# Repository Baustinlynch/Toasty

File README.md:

# Toasty Pad

## Features

- 3×3 grid
- 9 keys
- Minimalist design
- Keys can be programmed with macros using QMK

## PCB

I made my PCB using KiCad.

/\ PCB uses a ground plane so it looks like the gnd pins are not connected but they are :)

> This probably breaks many schematic/layout rules, but it looks like it will work.

## CAD

Printed in two pieces; looks pretty good. Made in Onshape.

## Firmware

This project uses QMK firmware included in this repository.

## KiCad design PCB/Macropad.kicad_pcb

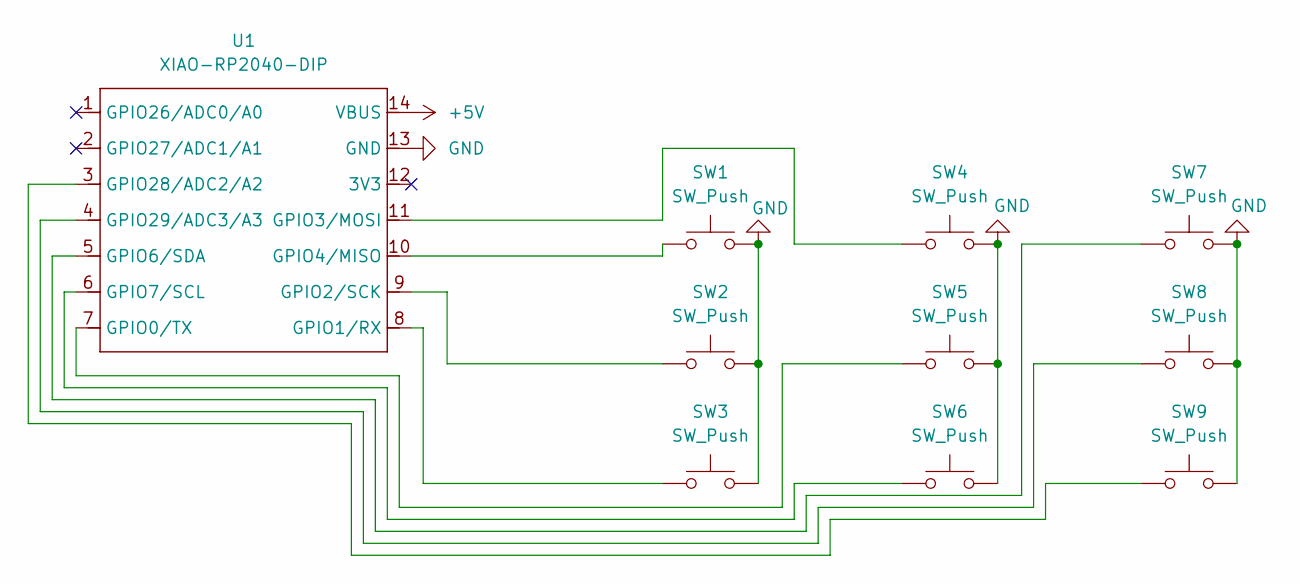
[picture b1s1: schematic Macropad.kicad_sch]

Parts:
SW1, SW2, SW3, SW4, SW5, SW6, SW7, SW8, SW9: SW_Push; SW_Cherry_MX_1.00u_PCB
U1: XIAO-RP2040-DIP

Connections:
+5V: U1.14 (VBUS)
GND: SW1.2, SW2.2, SW3.2, SW4.2, SW5.2, SW6.2, SW7.2, SW8.2, SW9.2, U1.13 (GND)
unnamed: SW5.1, U1.7 (GPIO0/TX)
unnamed: SW3.1, U1.8 (GPIO1/RX)
unnamed: SW2.1, U1.9 (GPIO2/SCK)
unnamed: SW4.1, U1.11 (GPIO3/MOSI)
unnamed: SW1.1, U1.10 (GPIO4/MISO)
unnamed: SW7.1, U1.5 (GPIO6/SDA)
unnamed: SW6.1, U1.6 (GPIO7/SCL)
unnamed: SW9.1, U1.3 (GPIO28/ADC2/A2)
unnamed: SW8.1, U1.4 (GPIO29/ADC3/A3)

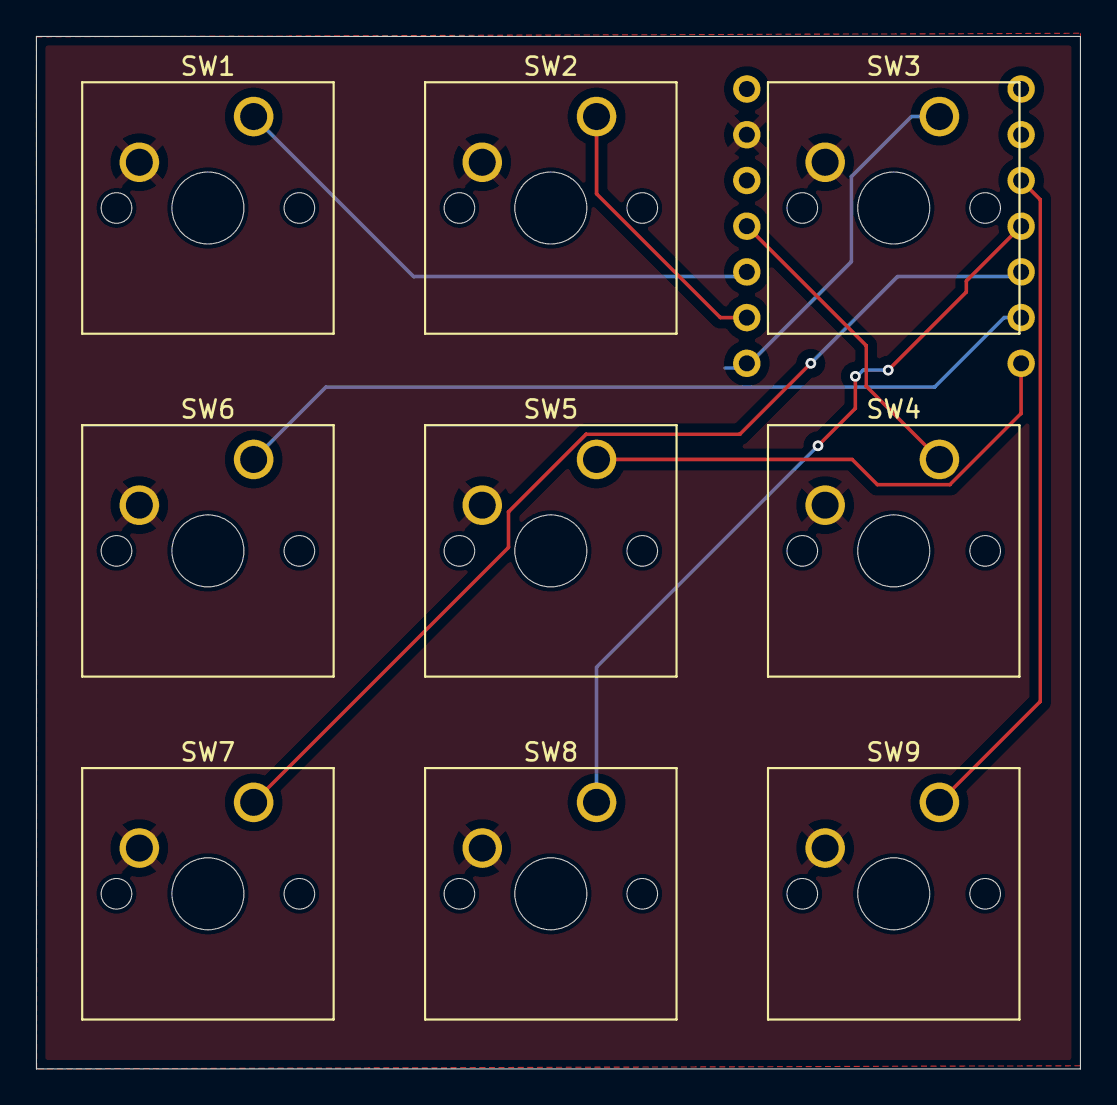
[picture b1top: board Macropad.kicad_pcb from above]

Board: 2 copper layers, 58.0 x 57.4 mm, 10 parts (1 on the bottom side), 10 nets.

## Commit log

2025-12-06 Create cad
2025-12-06 uploaded assembled
2025-12-06 Create pcb
2025-12-06 Create firm
2025-12-11 changed readme
2025-12-11 changes readme
2025-12-11 updated read me and added exploded assembly image
2025-12-12 fix: add missing newline in PCB section of README
